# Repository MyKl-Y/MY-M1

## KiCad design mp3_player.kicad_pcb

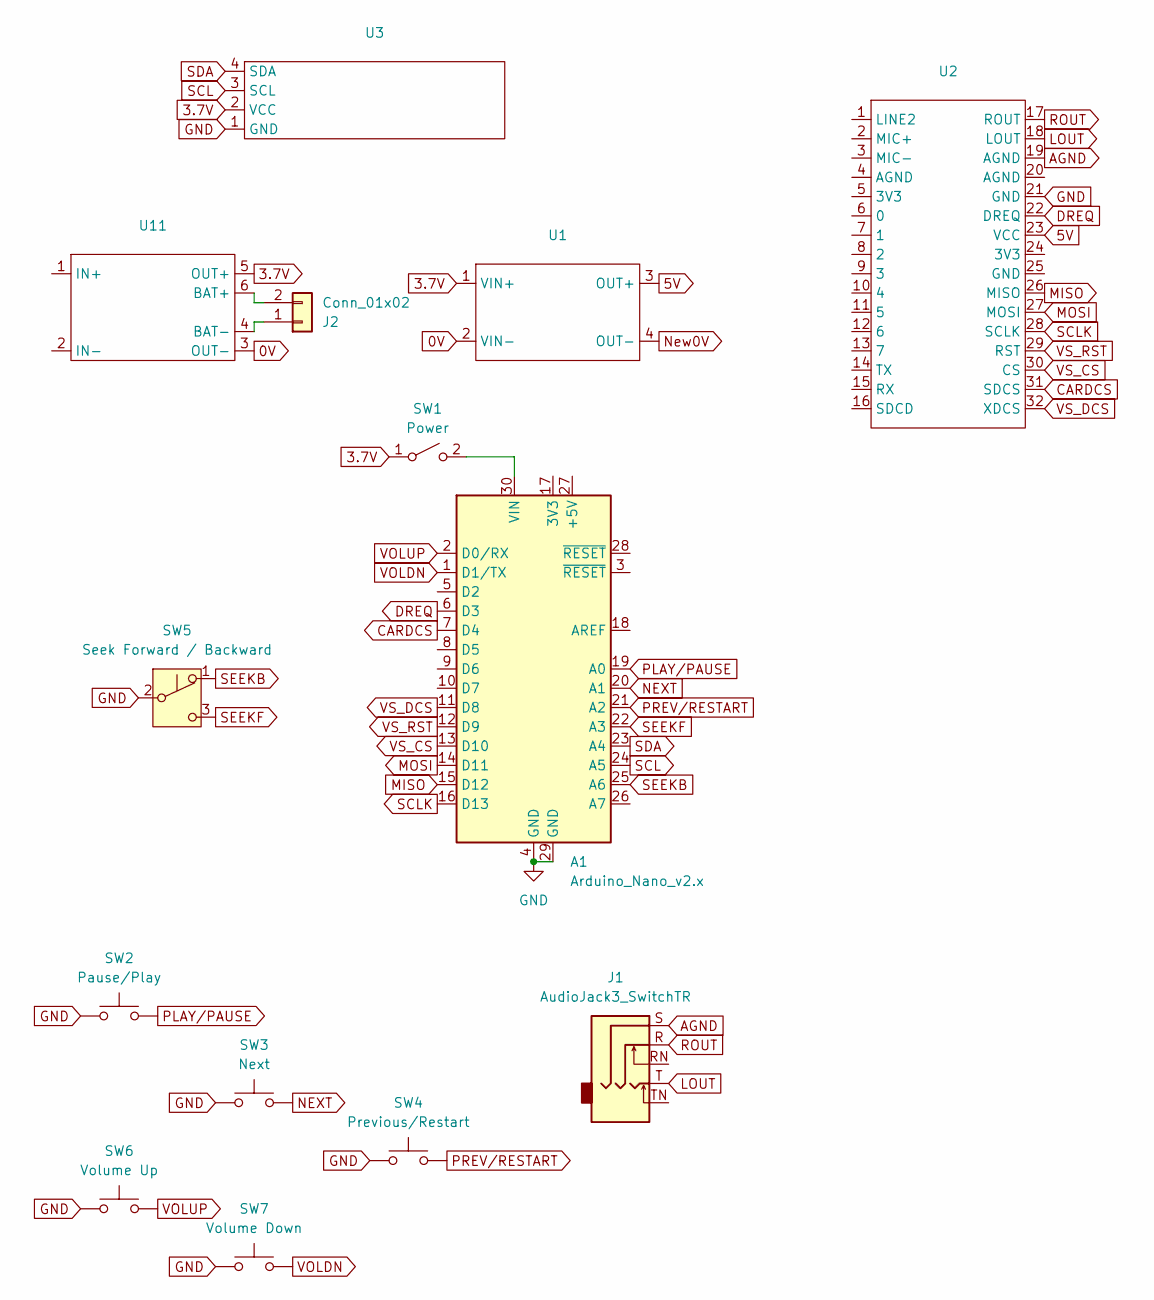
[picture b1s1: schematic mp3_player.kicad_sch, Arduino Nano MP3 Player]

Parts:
A1: Arduino_Nano_v2.x; Arduino_Nano
J1: AudioJack3_SwitchTR; Jack_3.5mm_CUI_SJ1-3525N_Horizontal
J2: Conn_01x02; JST_PH_S2B-PH-K_1x02_P2.00mm_Horizontal
SW1: Power; SW_DIP_SPSTx01_Slide_6.7x4.1mm_W7.62mm_P2.54mm_LowProfile
SW2: Pause/Play; SW_PUSH_6mm
SW3: Next; SW_PUSH_6mm
SW4: Previous/Restart; SW_PUSH_6mm
SW5: Seek Forward / Backward; SW_XKB_DM1-16UC-1
SW6: Volume Up; SW_Tactile_SPST_Angled_PTS645Vx39-2LFS
SW7: Volume Down; SW_Tactile_SPST_Angled_PTS645Vx39-2LFS
U1: MT3608_Step_Up_Boost_Converter
U2: Adafruit_VS1053_Breakout_Board
U3: SSD1306-0.91-OLED-4pin-128x32
U11: TP4056_LIPO_Charger_Protection_Module

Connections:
0V: U1.2 (VIN-), U11.3 (OUT-)
3.7V: SW1.1 (A), U1.1 (VIN+), U3.2 (VCC), U11.5 (OUT+)
5V: U1.3 (OUT+), U2.23 (VCC)
AGND: J1.S, U2.19 (AGND)
CARDCS: A1.7 (D4), U2.31 (SDCS)
DREQ: A1.6 (D3), U2.22 (DREQ)
GND: A1.4 (GND), A1.29 (GND), SW2.1, SW3.1, SW4.1, SW5.2 (B), SW6.1, SW7.1, U2.21 (GND), U3.1 (GND)
LOUT: J1.T, U2.18 (LOUT)
MISO: A1.15 (D12), U2.26 (MISO)
MOSI: A1.14 (D11), U2.27 (MOSI)
NEXT: A1.20 (A1), SW3.2
unnamed: A1.30 (VIN), SW1.2 (B)
unnamed: J2.1, U11.4 (BAT-)
unnamed: J2.2, U11.6 (BAT+)
New0V: U1.4 (OUT-)
PLAY/PAUSE: A1.19 (A0), SW2.2
PREV/RESTART: A1.21 (A2), SW4.2
ROUT: J1.R, U2.17 (ROUT)
SCL: A1.24 (A5), U3.3 (SCL)
SCLK: A1.16 (D13), U2.28 (SCLK)
SDA: A1.23 (A4), U3.4 (SDA)
SEEKB: A1.25 (A6), SW5.1 (A)
SEEKF: A1.22 (A3), SW5.3 (C)
VOLDN: A1.1 (D1/TX), SW7.2
VOLUP: A1.2 (D0/RX), SW6.2
VS_CS: A1.13 (D10), U2.30 (CS)
VS_DCS: A1.11 (D8), U2.32 (XDCS)
VS_RST: A1.12 (D9), U2.29 (RST)

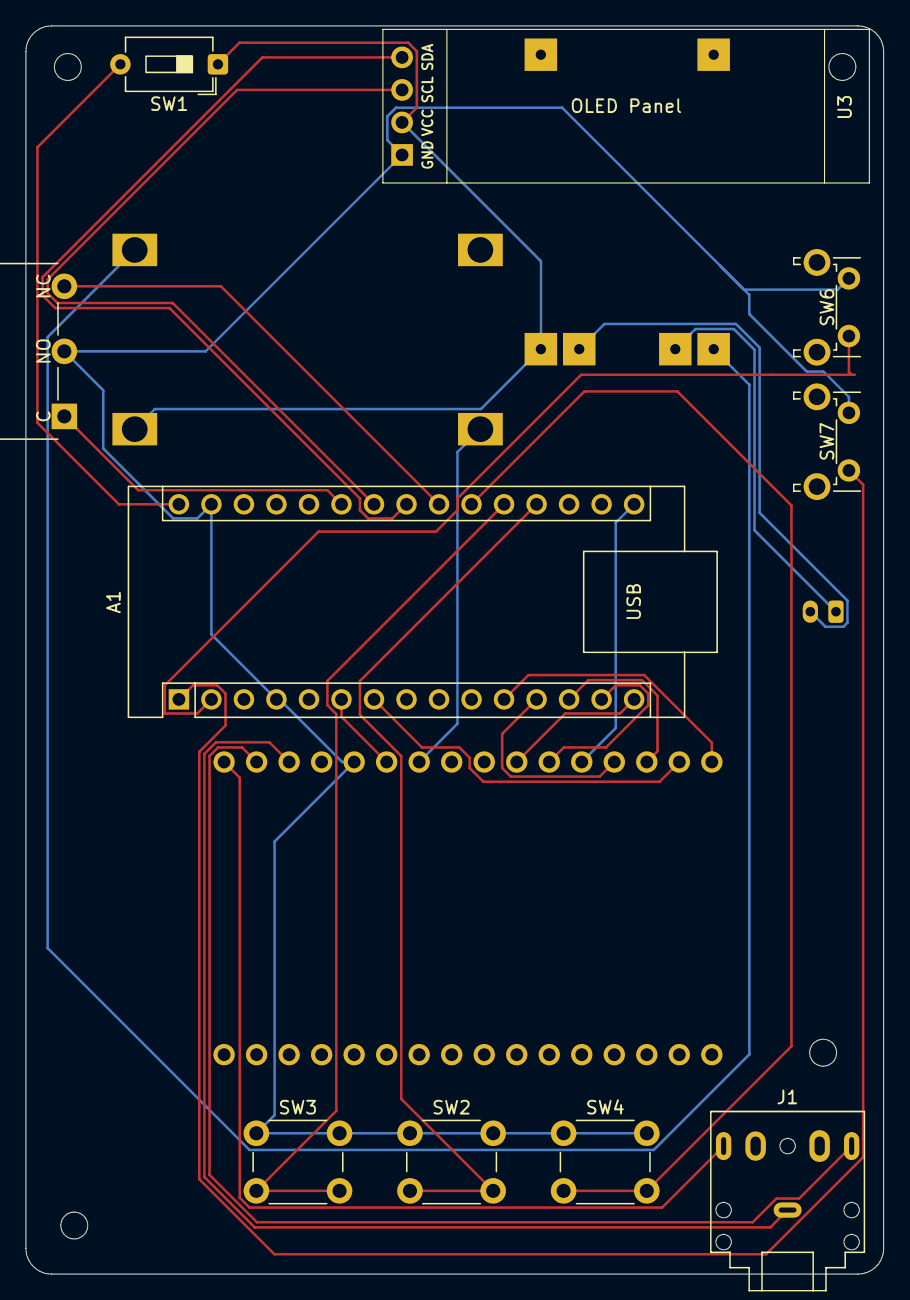
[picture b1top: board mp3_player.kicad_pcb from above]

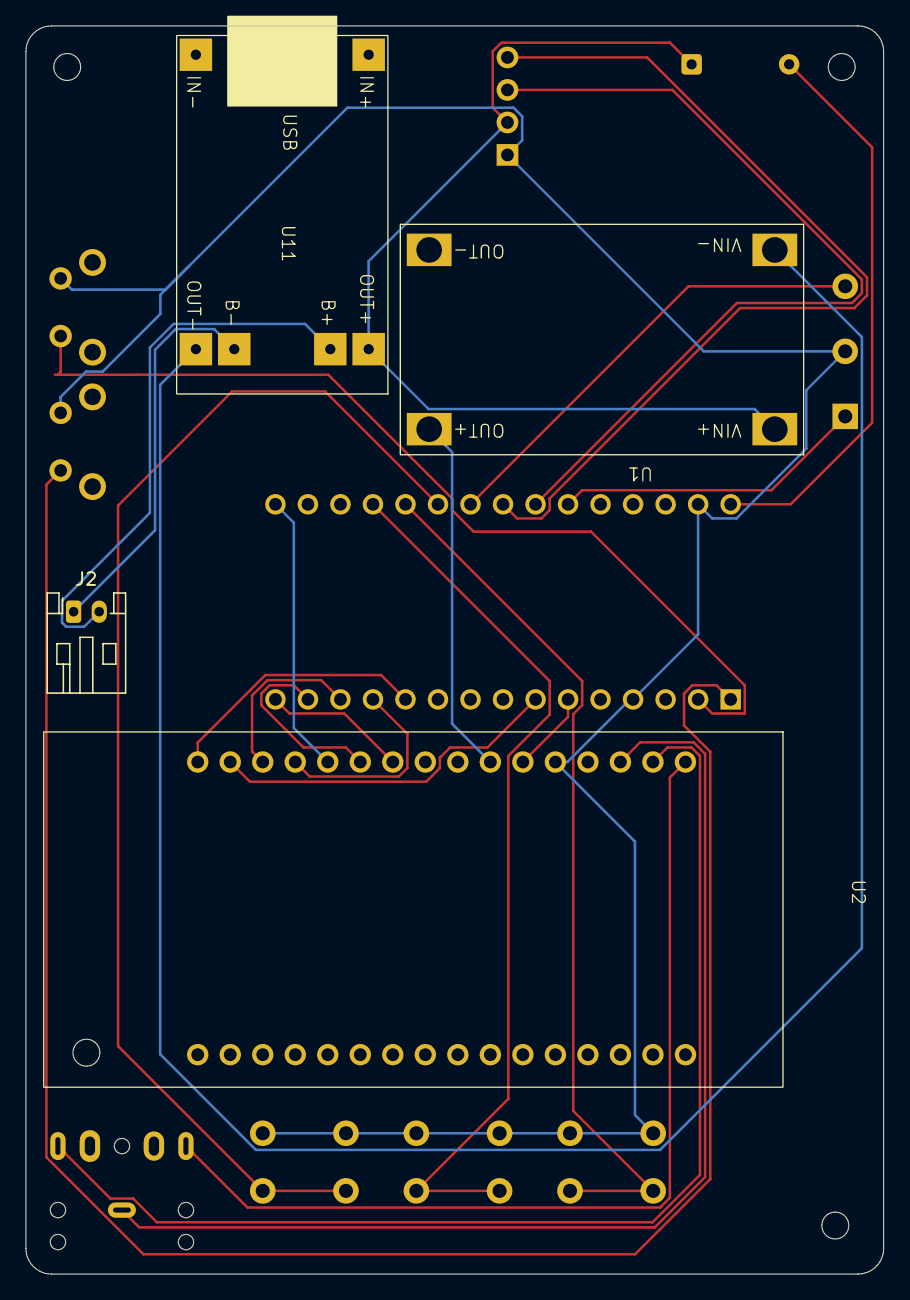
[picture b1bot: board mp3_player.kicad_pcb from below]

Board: 2 copper layers, 67.0 x 97.5 mm, 14 parts (4 on the bottom side), 27 nets.

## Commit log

2025-03-27 Sync work
2025-03-27 Hierarchical design for submodules
2025-04-08 Added OLED Display Module
2025-04-29 Code, drivers patch, and pcb updates
2025-04-30 Finish up PCB and send to manufacturer
2025-04-30 Play from last place
